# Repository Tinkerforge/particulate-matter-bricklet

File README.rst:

Particulate Matter Bricklet
===========================

This repository contains the firmware source code and the hardware design
files. The documentation generator configs can be found at
https://github.com/Tinkerforge/generators

Repository Content
------------------

software/:
 * examples/: Examples for all supported languages
 * build/: Compiled files
 * src/: Source code of firmware
 * Makefile: Makefile to build project

hardware/:
 * Contains KiCad project files and additionally schematics as PDF

datasheets/:
 * Contains datasheets for sensors and complex ICs that are used

Hardware
--------

The hardware is designed with the open source EDA Suite KiCad
(http://www.kicad.org). Before you are able to open the files,
you have to install the Tinkerforge kicad-libraries
(https://github.com/Tinkerforge/kicad-libraries). You can either clone
them directly in hardware/ or clone them in a separate folder and
symlink them into hardware/
(ln -s kicad_path/kicad-libraries project_path/hardware). After that you
can open the .pro file in hardware/ with KiCad and from there view and
modify the schematics and the PCB layout.

Software
--------

If you want to do your own Brick/Bricklet firmware development we highly
recommend that you use our build environment setup script and read the
tutorial (https://www.tinkerforge.com/en/doc/Tutorials/Tutorial_Build_Environment/Tutorial.html).

To compile the C code we recommend you to install the newest GNU Arm Embedded
Toolchain (https://launchpad.net/gcc-arm-embedded/+download).
You also need to install bricklib2 (https://github.com/Tinkerforge/bricklib2).

You can either clone it directly in software/src/ or clone it in a
separate folder and symlink it into software/src/
(ln -s bricklib_path/bricklib2 project_path/software/src/). Finally make sure to
have CMake installed (http://www.cmake.org/cmake/resources/software.html).

After that you can build the firmware by invoking make in software/.
The firmware (.zbin) can then be found in software/build/ and uploaded
with brickv (click button "Flashing" on start screen).

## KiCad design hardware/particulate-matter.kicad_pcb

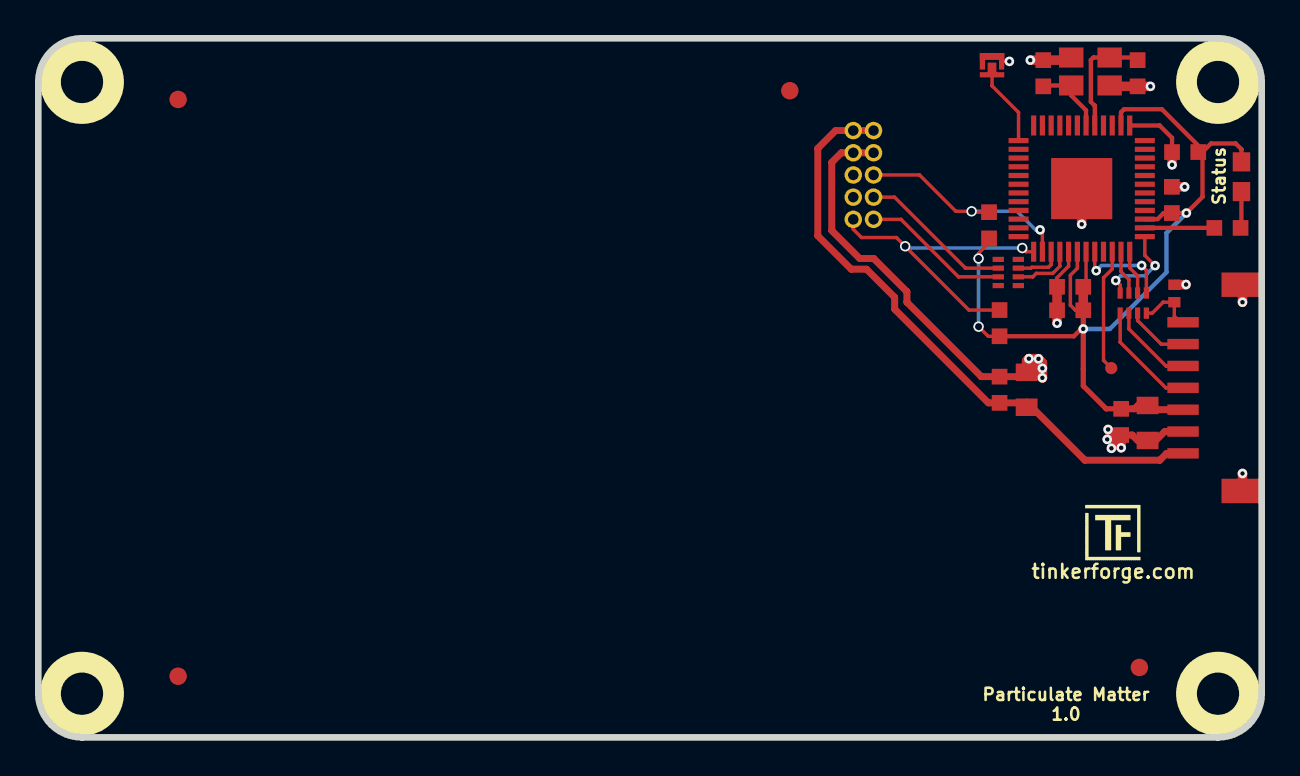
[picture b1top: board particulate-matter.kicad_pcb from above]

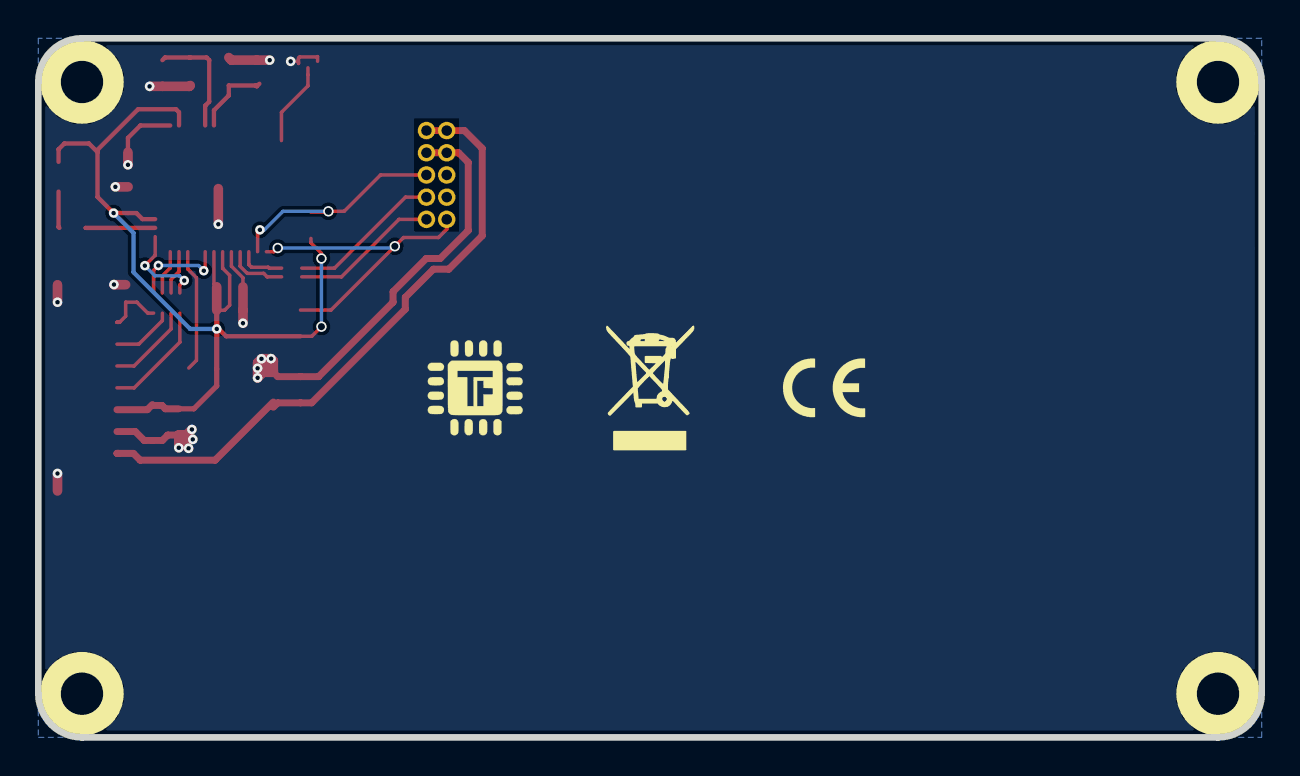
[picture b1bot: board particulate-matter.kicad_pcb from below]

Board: 2 copper layers, 70.0 x 40.0 mm, 33 parts (2 on the bottom side), 23 nets.

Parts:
C1, C11: 10uF; C0805
C2: 1uF; C0603F
C3, C4, C5: 100nF; C0603F
C6: 220nF; C0603F
C7: 220pF; C0402F
C8, C9: 10pF; C0603F
C10: 100n; C0603F
D3: blue; D0603E
Fiducial_Mark: VAL**; Fiducial_Mark
Fiducial_Mark#2, Fiducial_Mark#3, Fiducial_Mark#4: VAL**; Fiducial_Mark
P1: CON-SENSOR2
P2: BOOT; SolderJumper
P3: DEBUG; DEBUG_PAD
R1: 1k; R0603F
R2, R3: 10k; R0603F
RP1: 82; 4X0402
RP2: 100; 4X0402
U1: XMC1404; QFN48-EP2
U2, U3, U4, U5: DRILL; DRILL_NP
U6: PMS7003
VAL: CE_5mm
VAL#2: WEEE_7mm
X1: 16MHz; CRYSTAL_3225

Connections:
+5V: C10.1, C11.2, P1.1, U6.1, U6.2
GND: C1.1, C2.1, C3.2, C4.2, C5.2, C6.2, C7.2, C8.2, C9.2, C10.2, C11.1, P1.2, P1.EP, P2.1, U1.17, U1.37, U1.EP, U6.3, U6.4, X1.3
unnamed: C7.1, P1.7, RP1.4
unnamed: C8.1, U1.41, X1.2
unnamed: C9.1, U1.42, X1.1
unnamed: D3.2, R1.2
unnamed: P1.4, RP1.1
unnamed: P1.5, RP1.2
unnamed: P1.6, RP1.3
unnamed: P2.2, U1.1
unnamed: P3.1, U1.22
unnamed: R1.1, U1.26
unnamed: RP2.6, U6.7
unnamed: RP2.7, U6.9
PMS_RESET: R3.2, U1.14, U6.5
PMS_RX: RP2.2, U1.16
PMS_SET: R2.2, U1.13, U6.10
PMS_TX: RP2.3, U1.15
S-CLK: RP1.7, U1.23
S-CS: RP1.8, U1.25
S-MISO: RP1.5, U1.20
S-MOSI: RP1.6, U1.24
VCC: C1.2, C2.2, C3.1, C4.1, C5.1, C6.1, D3.1, P1.3, R2.1, R3.1, U1.18, U1.19, U1.27, U1.38

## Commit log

2018-01-08 initial checkin
2018-01-08 Fix readme
2018-01-08 Add datasheet (chinese)
2018-01-08 Add initial version
2018-01-09 Change CoMCU from XMC1100 to XMC1400
2018-01-09 Annotate components
2018-01-09 Add initial version of PCB
2018-01-09 Assign components to library
2018-01-09 Add resistors for TX/RX and another capacitor for the PMS Sensor
2018-01-09 add fiducial marks
2018-01-09 fix pms footprint, add title
2018-01-09 updating pms footprint
2018-01-19 add errata
2018-01-22 Remove R2, change footprint of RP1
2018-01-22 Fix ground routing of U6, move debug pad & C10-C11, move U6 to the edge
2018-02-20 Add .gitignore
2018-02-20 Cleanup KiCad libraries config
    Ensure LibDir=kicad-libraries and LibName1=tinkerforge.
    Remove special library.
2018-03-09 fix Status text, fix board name
2018-03-09 Add initial software stub implementation
2018-03-09 Add basic PM7003 read-out functionality
2018-03-09 implement fixed footprint
2018-03-15 fix logo positions
2018-03-15 Change flash size and pins to be compatible with production unit
2018-03-16 Remove debug code
2018-03-16 Add communication logic to realise Bricklet API
2018-03-27 specify processor
2018-04-23 Add 3d information (final)
2018-04-23 Add 3d model (*.FCStd & *.step)
2018-05-04 Add schematic PDF
2018-05-29 Define flash size to be 64KB
2018-06-04 Turn debug off
2018-06-05 Add examples
2018-06-07 Update changelog for initial release
2018-06-14 Add english language version of datasheet
2018-06-18 Fix footprint
2018-07-11 Add Makefile with docker support
2018-07-11 Update directory structure and build instructions
2018-07-11 Remove obsolete generate_makefile scripts
2018-09-14 vbnet: Fix typo in comment
2018-10-04 Increase version for new release (changes in bricklib2)
2018-10-04 Add rev to changelog
2018-11-06 Add rust examples
2018-11-07 rust: Accept host names for ip connection, fix naming inconsistencies
2018-11-07 rust: Rename callback receivers.
2018-12-14 Add go examples.
2018-12-18 go: Change import path.
2018-12-18 go: Change import path again.
2018-12-20 rust: Fix result variable names in examples.
2019-01-24 mqtt: Add examples.
2019-01-24 mqtt: Fix example header.
2019-01-24 mqtt: Remove executable bit in example permissions.
2019-01-24 go: Minor example fixes.
2019-01-24 mqtt: Minor example fixes.
2019-03-28 mqtt: Fix whitespace.
2019-08-22 c: Adapt to bindings changes
2020-01-13 examples: Use python3 input instead of python2 raw_input.
2020-01-13 examples: mqtt: Remove trailing whitespace.
2020-08-19 Add uc examples.
2020-08-25 uc: Fix whitespace
2020-08-27 uc: Fix warnings.
2020-08-31 uc: Use fixed-with placeholders in format strings.
2020-09-02 uc: Add example driver note.
2021-10-25 Update KiCad link
    https://www.kicad.org/blog/2021/10/Avoid-links-to-former-kicad-domain/
2022-04-19 examples: uc: Rename TF_HalContext to TF_HAL.
2022-04-27 uc: Adapt to bindings changes
2022-05-10 go: Fix format string
2022-07-06 Add license files.
2025-10-04 Fix compatibility with new Docker build image (GCC 14.2.1)

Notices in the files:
hardware/particulate-matter.kicad_pcb:
Licensed under CERN OHL v.1.1
Copyright (©) 2018, L.Lauer
Copyright Tinkerforge GmbH 2018.
This documentation describes Open Hardware and is licensed under the
CERN OHL v. 1.1.
